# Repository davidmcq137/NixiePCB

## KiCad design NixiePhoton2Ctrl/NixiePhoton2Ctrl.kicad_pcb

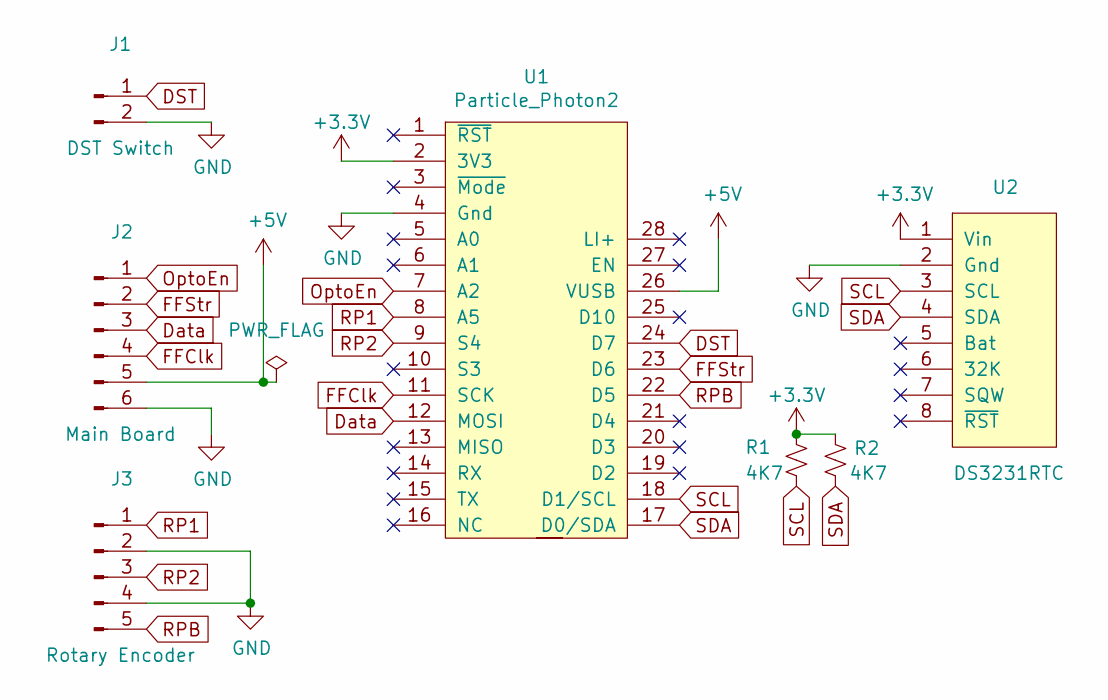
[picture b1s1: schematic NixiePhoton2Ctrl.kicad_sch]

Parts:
J1: DST Switch; PinHeader_1x02_P2.54mm_Vertical
J2: Main Board; PinHeader_1x06_P2.54mm_Vertical
J3: Rotary Encoder; PinHeader_1x05_P2.54mm_Vertical
R1, R2: 4K7; R_Axial_DIN0207_L6.3mm_D2.5mm_P7.62mm_Horizontal
U1: Particle_Photon2
U2: DS3231RTC

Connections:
+3V3: R1.1, R2.1, U1.2 (3V3), U2.1 (Vin)
+5V: J2.5, U1.26 (VUSB)
DST: J1.1, U1.24 (D7)
Data: J2.3, U1.12 (MOSI)
FFClk: J2.4, U1.11 (SCK)
FFStr: J2.2, U1.23 (D6)
GND: J1.2, J2.6, J3.2, J3.4, U1.4 (Gnd), U2.2 (Gnd)
OptoEn: J2.1, U1.7 (A2)
RP1: J3.1, U1.8 (A5)
RP2: J3.3, U1.9 (S4)
RPB: J3.5, U1.22 (D5)
SCL: R1.2, U1.18 (D1/SCL), U2.3 (SCL)
SDA: R2.2, U1.17 (D0/SDA), U2.4 (SDA)

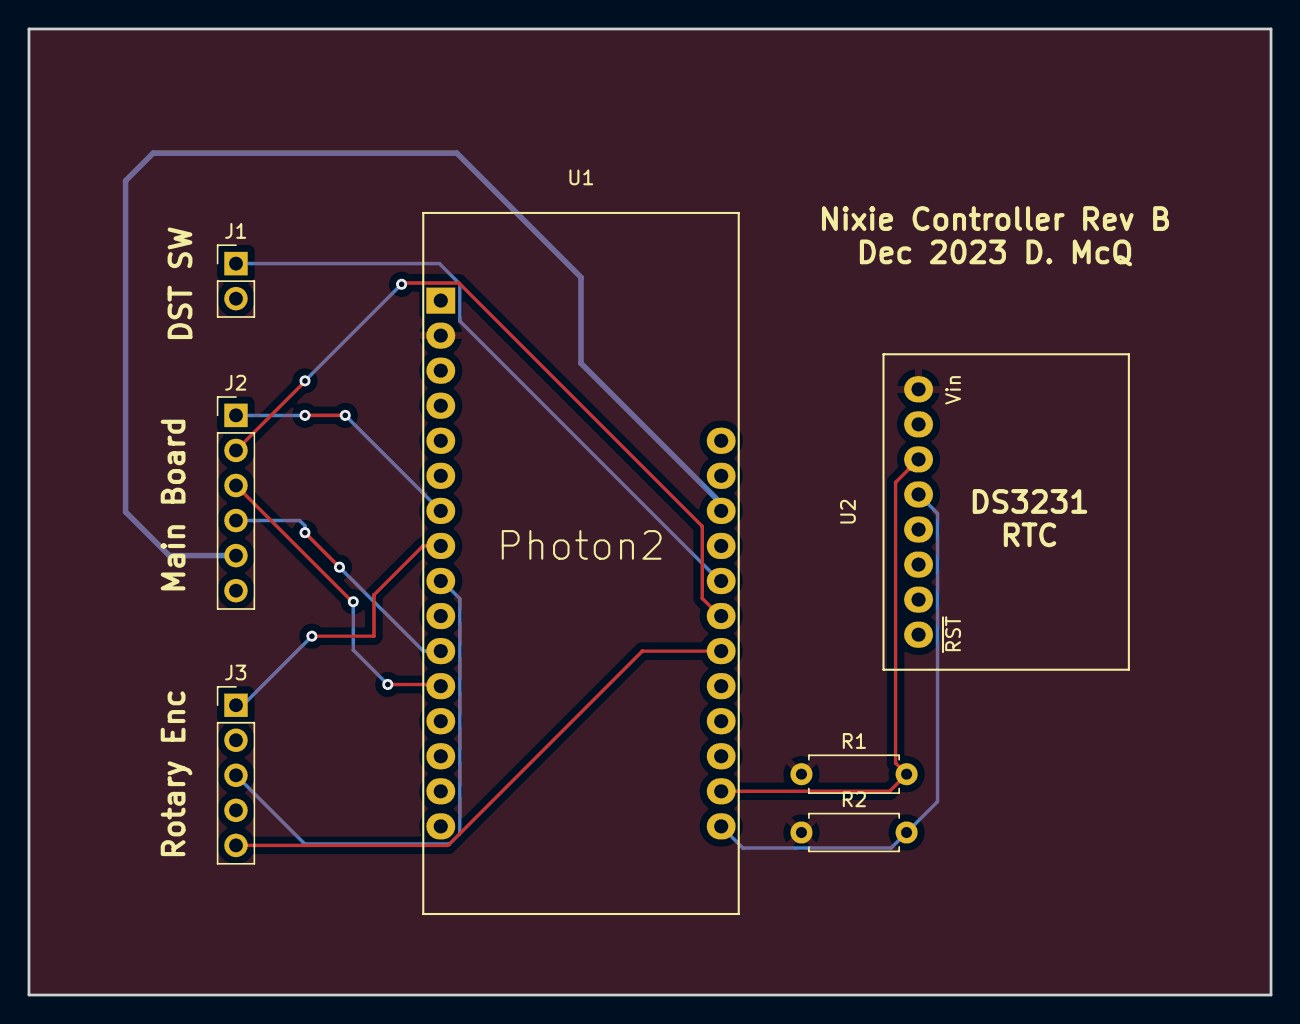
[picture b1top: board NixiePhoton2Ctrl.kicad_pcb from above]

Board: 2 copper layers, 90.0 x 70.0 mm, 7 parts (0 on the bottom side), 13 nets.

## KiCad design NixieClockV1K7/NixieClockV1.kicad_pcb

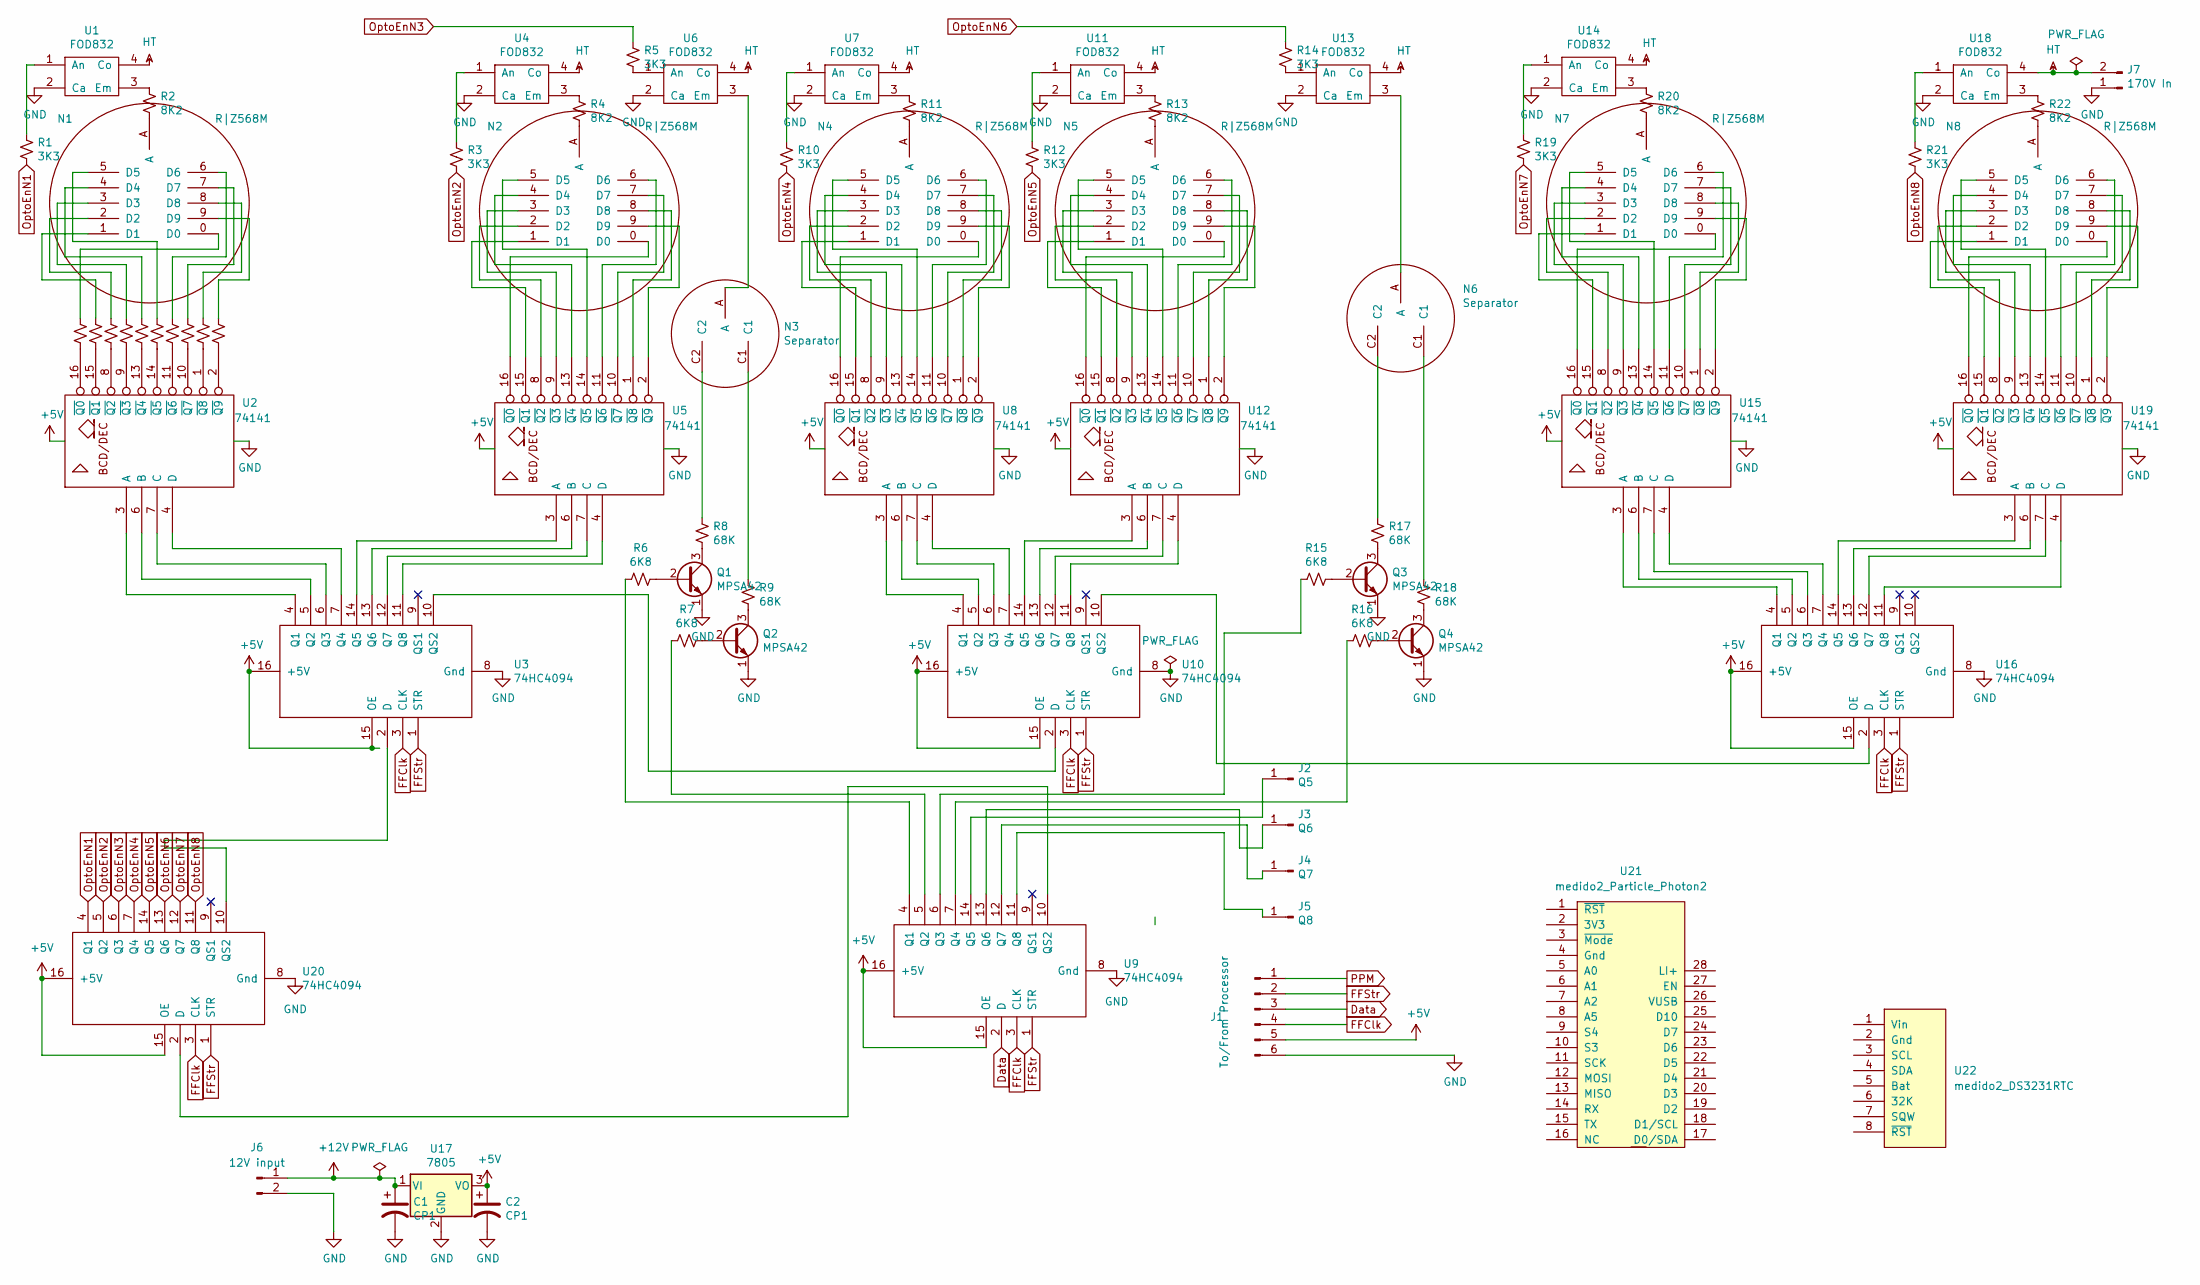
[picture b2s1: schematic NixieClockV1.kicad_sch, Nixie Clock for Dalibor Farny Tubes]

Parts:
C1, C2: CP1; CP_Radial_D7.5mm_P2.50mm
J1: To/From Processor; PinHeader_1x06_P2.54mm_Vertical
J2: Q5; PinHeader_1x01_P2.54mm_Vertical
J3: Q6; PinHeader_1x01_P2.54mm_Vertical
J4: Q7; PinHeader_1x01_P2.54mm_Vertical
J5: Q8; PinHeader_1x01_P2.54mm_Vertical
J6: 12V input; PinHeader_1x02_P2.54mm_Vertical
J7: 170V In; PinHeader_1x02_P2.54mm_Vertical
N1, N2, N4, N5, N7, N8: R|Z568M; RZ568M
N3, N6: Separator
Q1, Q2, Q3, Q4: MPSA42; TO-92L_Inline_Wide
R1, R3, R5, R10, R12, R14, R19, R21: 3K3; R_Axial_DIN0207_L6.3mm_D2.5mm_P10.16mm_Horizontal
R2, R4, R11, R13, R20, R22: 8K2; R_Axial_DIN0207_L6.3mm_D2.5mm_P10.16mm_Horizontal
R6, R7, R15, R16: 6K8; R_Axial_DIN0207_L6.3mm_D2.5mm_P10.16mm_Horizontal
R8, R9, R17, R18: 68K; R_Axial_DIN0207_L6.3mm_D2.5mm_P10.16mm_Horizontal
R23: 1; R_1210_3225Metric_Pad1.30x2.65mm_HandSolder
R24, R25, R26, R27, R28, R29, R30, R31, R32: R_Small_US; R_1210_3225Metric_Pad1.30x2.65mm_HandSolder
U1, U4, U6, U7, U11, U13, U14, U18: FOD832; DIP-4_W7.62mm
U2, U5, U8, U12, U15, U19: 74141; DIP-16_W7.62mm_Socket
U3, U9, U10, U20: 74HC4094; DIP-16_W7.62mm
U16: 74HC4094; DIP-16_W7.62mm_Socket
U17: 7805; TO-220-3_Vertical
U21: medido2_Particle_Photon2
U22: medido2_DS3231RTC

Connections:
+12V: C1.1, J6.1, U17.1 (VI)
Data: J1.3, U9.2 (D)
FFClk: J1.4, U3.3 (CLK), U9.3 (CLK), U10.3 (CLK), U16.3 (CLK), U20.3 (CLK)
FFStr: J1.2, U3.1 (STR), U9.1 (STR), U10.1 (STR), U16.1 (STR), U20.1 (STR)
GND: C1.2, C2.2, J1.6, J6.2, J7.1, Q1.1 (E), Q2.1 (E), Q3.1 (E), Q4.1 (E), U1.2 (Ca), U2.12 (GND), U3.8 (Gnd), U4.2 (Ca), U5.12 (GND), U6.2 (Ca), U7.2 (Ca), U8.12 (GND), U9.8 (Gnd), U10.8 (Gnd), U11.2 (Ca), U12.12 (GND), U13.2 (Ca), U14.2 (Ca), U15.12 (GND), U16.8 (Gnd), U17.2 (GND), U18.2 (Ca), U19.12 (GND), U20.8 (Gnd)
HT: J7.2, U1.4 (Co), U4.4 (Co), U6.4 (Co), U7.4 (Co), U11.4 (Co), U13.4 (Co), U14.4 (Co), U18.4 (Co)
unnamed: J2.1, U9.14 (Q5)
unnamed: J3.1, U9.13 (Q6)
unnamed: J4.1, U9.12 (Q7)
unnamed: J5.1, U9.11 (Q8)
unnamed: N1.0 (D0), R23.1
unnamed: N1.1 (D1), R24.2
unnamed: N1.2 (D2), R25.1
unnamed: N1.3 (D3), R26.1
unnamed: N1.4 (D4), R27.1
unnamed: N1.5 (D5), R28.1
unnamed: N1.6 (D6), R29.1
unnamed: N1.7 (D7), R30.1
unnamed: N1.8 (D8), R31.1
unnamed: N1.9 (D9), R32.1
unnamed: N1.A, R2.2
unnamed: N2.0 (D0), U5.16 (~Q0)
unnamed: N2.1 (D1), U5.15 (~Q1)
unnamed: N2.2 (D2), U5.8 (~Q2)
unnamed: N2.3 (D3), U5.9 (~Q3)
unnamed: N2.4 (D4), U5.13 (~Q4)
unnamed: N2.5 (D5), U5.14 (~Q5)
unnamed: N2.6 (D6), U5.11 (~Q6)
unnamed: N2.7 (D7), U5.10 (~Q7)
unnamed: N2.8 (D8), U5.1 (~Q8)
unnamed: N2.9 (D9), U5.2 (~Q9)
unnamed: N2.A, R4.2
unnamed: N3.C1, R9.1
unnamed: N3.C2, R8.1
unnamed: N4.0 (D0), U8.16 (~Q0)
unnamed: N4.1 (D1), U8.15 (~Q1)
unnamed: N4.2 (D2), U8.8 (~Q2)
unnamed: N4.3 (D3), U8.9 (~Q3)
unnamed: N4.4 (D4), U8.13 (~Q4)
unnamed: N4.5 (D5), U8.14 (~Q5)
unnamed: N4.6 (D6), U8.11 (~Q6)
unnamed: N4.7 (D7), U8.10 (~Q7)
unnamed: N4.8 (D8), U8.1 (~Q8)
unnamed: N4.9 (D9), U8.2 (~Q9)
unnamed: N4.A, R11.2
unnamed: N5.0 (D0), U12.16 (~Q0)
unnamed: N5.1 (D1), U12.15 (~Q1)
unnamed: N5.2 (D2), U12.8 (~Q2)
unnamed: N5.3 (D3), U12.9 (~Q3)
unnamed: N5.4 (D4), U12.13 (~Q4)
unnamed: N5.5 (D5), U12.14 (~Q5)
unnamed: N5.6 (D6), U12.11 (~Q6)
unnamed: N5.7 (D7), U12.10 (~Q7)
unnamed: N5.8 (D8), U12.1 (~Q8)
unnamed: N5.9 (D9), U12.2 (~Q9)
unnamed: N5.A, R13.2
unnamed: N6.C1, R18.1
unnamed: N6.C2, R17.1
unnamed: N7.0 (D0), U15.16 (~Q0)
unnamed: N7.1 (D1), U15.15 (~Q1)
unnamed: N7.2 (D2), U15.8 (~Q2)
unnamed: N7.3 (D3), U15.9 (~Q3)
unnamed: N7.4 (D4), U15.13 (~Q4)
unnamed: N7.5 (D5), U15.14 (~Q5)
unnamed: N7.6 (D6), U15.11 (~Q6)
unnamed: N7.7 (D7), U15.10 (~Q7)
unnamed: N7.8 (D8), U15.1 (~Q8)
unnamed: N7.9 (D9), U15.2 (~Q9)
unnamed: N7.A, R20.2
unnamed: N8.0 (D0), U19.16 (~Q0)
unnamed: N8.1 (D1), U19.15 (~Q1)
unnamed: N8.2 (D2), U19.8 (~Q2)
unnamed: N8.3 (D3), U19.9 (~Q3)
unnamed: N8.4 (D4), U19.13 (~Q4)
unnamed: N8.5 (D5), U19.14 (~Q5)
unnamed: N8.6 (D6), U19.11 (~Q6)
unnamed: N8.7 (D7), U19.10 (~Q7)
unnamed: N8.8 (D8), U19.1 (~Q8)
unnamed: N8.9 (D9), U19.2 (~Q9)
unnamed: N8.A, R22.2
unnamed: Q1.2 (B), R6.1
unnamed: Q1.3 (C), R8.2
unnamed: Q2.2 (B), R7.1
unnamed: Q2.3 (C), R9.2
unnamed: Q3.2 (B), R15.1
unnamed: Q3.3 (C), R17.2
unnamed: Q4.2 (B), R16.1
unnamed: Q4.3 (C), R18.2
unnamed: R1.1, U1.1 (An)
unnamed: R2.1, U1.3 (Em)
unnamed: U2.3 (A), U3.4 (Q1)
unnamed: U2.6 (B), U3.5 (Q2)
unnamed: U2.7 (C), U3.6 (Q3)
unnamed: U2.4 (D), U3.7 (Q4)
unnamed: R23.2, U2.16 (~Q0)
unnamed: R24.1, U2.15 (~Q1)
unnamed: R25.2, U2.8 (~Q2)
unnamed: R26.2, U2.9 (~Q3)
unnamed: R27.2, U2.13 (~Q4)
unnamed: R28.2, U2.14 (~Q5)
unnamed: R29.2, U2.11 (~Q6)
unnamed: R30.2, U2.10 (~Q7)
unnamed: R31.2, U2.1 (~Q8)
unnamed: R32.2, U2.2 (~Q9)
unnamed: U3.14 (Q5), U5.3 (A)
unnamed: U3.13 (Q6), U5.6 (B)
unnamed: U3.12 (Q7), U5.7 (C)
unnamed: U3.11 (Q8), U5.4 (D)
unnamed: R3.1, U4.1 (An)
unnamed: R4.1, U4.3 (Em)
unnamed: R5.2, U6.1 (An)
unnamed: N3.A, U6.3 (Em)
unnamed: R10.1, U7.1 (An)
unnamed: R11.1, U7.3 (Em)
unnamed: R6.2, U9.4 (Q1)
unnamed: R7.2, U9.5 (Q2)
unnamed: R15.2, U9.6 (Q3)
unnamed: R16.2, U9.7 (Q4)
unnamed: U3.10 (QS2), U10.2 (D)
unnamed: U8.3 (A), U10.4 (Q1)
unnamed: U8.6 (B), U10.5 (Q2)
unnamed: U8.7 (C), U10.6 (Q3)
unnamed: U8.4 (D), U10.7 (Q4)
unnamed: U10.14 (Q5), U12.3 (A)
unnamed: U10.13 (Q6), U12.6 (B)
unnamed: U10.12 (Q7), U12.7 (C)
unnamed: U10.11 (Q8), U12.4 (D)
unnamed: U10.10 (QS2), U16.2 (D)
unnamed: R12.1, U11.1 (An)
unnamed: R13.1, U11.3 (Em)
unnamed: R14.2, U13.1 (An)
unnamed: N6.A, U13.3 (Em)
unnamed: R19.1, U14.1 (An)
unnamed: R20.1, U14.3 (Em)
unnamed: U15.3 (A), U16.4 (Q1)
unnamed: U15.6 (B), U16.5 (Q2)
unnamed: U15.7 (C), U16.6 (Q3)
unnamed: U15.4 (D), U16.7 (Q4)
unnamed: U16.14 (Q5), U19.3 (A)
unnamed: U16.13 (Q6), U19.6 (B)
unnamed: U16.12 (Q7), U19.7 (C)
unnamed: U16.11 (Q8), U19.4 (D)
unnamed: R21.1, U18.1 (An)
unnamed: R22.1, U18.3 (Em)
unnamed: U9.10 (QS2), U20.2 (D)
unnamed: U3.2 (D), U20.10 (QS2)
OptoEnN1: R1.2, U20.4 (Q1)
OptoEnN2: R3.2, U20.5 (Q2)
OptoEnN3: R5.1, U20.6 (Q3)
OptoEnN4: R10.2, U20.7 (Q4)
OptoEnN5: R12.2, U20.14 (Q5)
OptoEnN6: R14.1, U20.13 (Q6)
OptoEnN7: R19.2, U20.12 (Q7)
OptoEnN8: R21.2, U20.11 (Q8)
PPM: J1.1

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
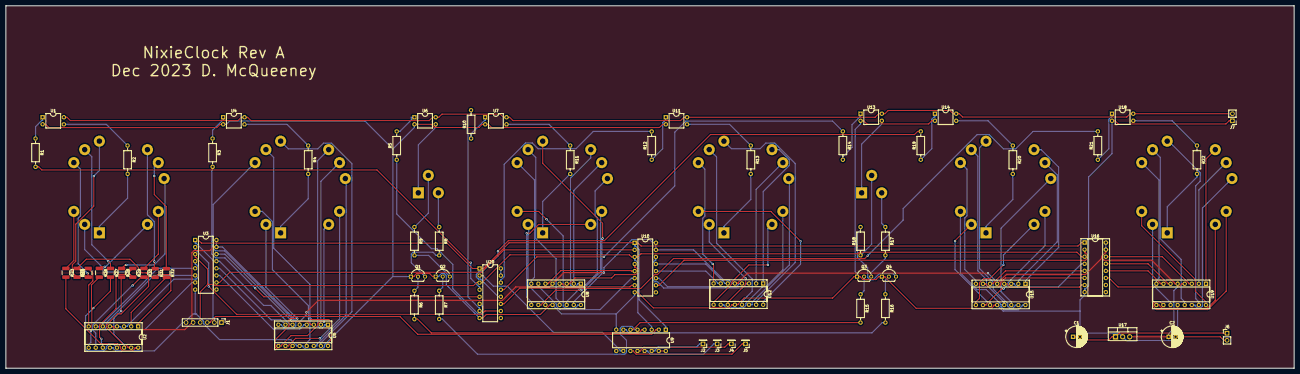
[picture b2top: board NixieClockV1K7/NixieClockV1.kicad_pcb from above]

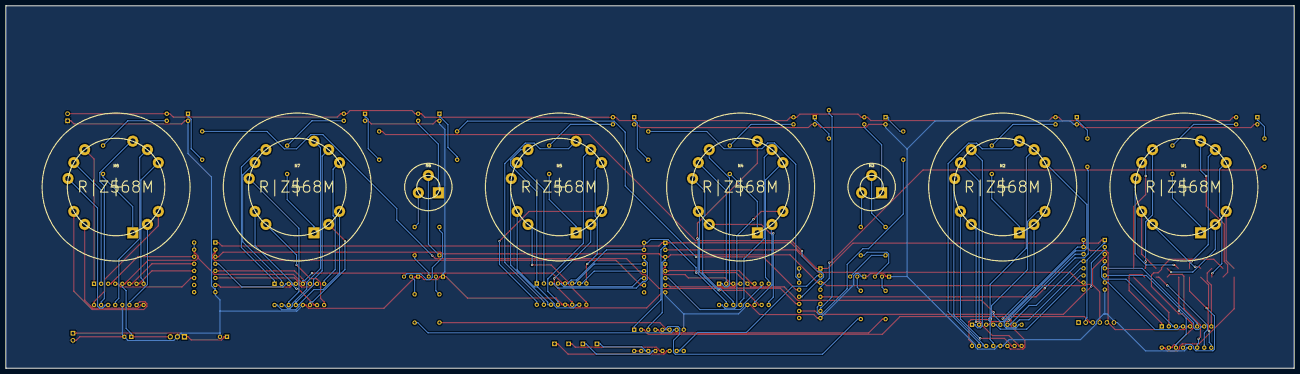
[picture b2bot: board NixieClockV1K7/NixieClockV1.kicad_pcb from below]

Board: 2 copper layers, 462.1 x 130.0 mm, 73 parts (8 on the bottom side), 157 nets.

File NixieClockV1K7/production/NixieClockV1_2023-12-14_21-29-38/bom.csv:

Designator,Footprint,Quantity,Value,LCSC Part #
"C1, C2",CP_Radial_D7.5mm_P2.50mm,2,CP1,
J1,PinHeader_1x06_P2.54mm_Vertical,1,To/From Processor,
J2,PinHeader_1x01_P2.54mm_Vertical,1,Q5,
J3,PinHeader_1x01_P2.54mm_Vertical,1,Q6,
J4,PinHeader_1x01_P2.54mm_Vertical,1,Q7,
J5,PinHeader_1x01_P2.54mm_Vertical,1,Q8,
J6,PinHeader_1x02_P2.54mm_Vertical,1,12V input,
J7,PinHeader_1x02_P2.54mm_Vertical,1,170V In,
"N1, N2, N4, N5, N7, N8",RZ568M,6,R|Z568M,
"N3, N6",Separator,2,Separator,
"Q1, Q2, Q3, Q4",TO-92L_Inline_Wide,4,MPSA42,
"R1, R10, R12, R14, R19, R21, R3, R5",R_Axial_DIN0207_L6.3mm_D2.5mm_P10.16mm_Horizontal,8,3K3,
"R11, R13, R2, R20, R22, R4",R_Axial_DIN0207_L6.3mm_D2.5mm_P10.16mm_Horizontal,6,8K2,
"R15, R16, R6, R7",R_Axial_DIN0207_L6.3mm_D2.5mm_P10.16mm_Horizontal,4,6K8,
"R17, R18, R8, R9",R_Axial_DIN0207_L6.3mm_D2.5mm_P10.16mm_Horizontal,4,68K,
R23,1210,1,1,
"R24, R25, R26, R27, R28, R29, R30, R31, R32",1210,9,R_Small_US,
"U1, U11, U13, U14, U18, U4, U6, U7",DIP-4_W7.62mm,8,FOD832,
"U10, U20, U3, U9",DIP-16_W7.62mm,4,74HC4094,
"U12, U15, U19, U2, U5, U8",DIP-16_W7.62mm_Socket,6,74141,
U16,DIP-16_W7.62mm_Socket,1,74HC4094,
U17,TO-220-3_Vertical,1,7805,

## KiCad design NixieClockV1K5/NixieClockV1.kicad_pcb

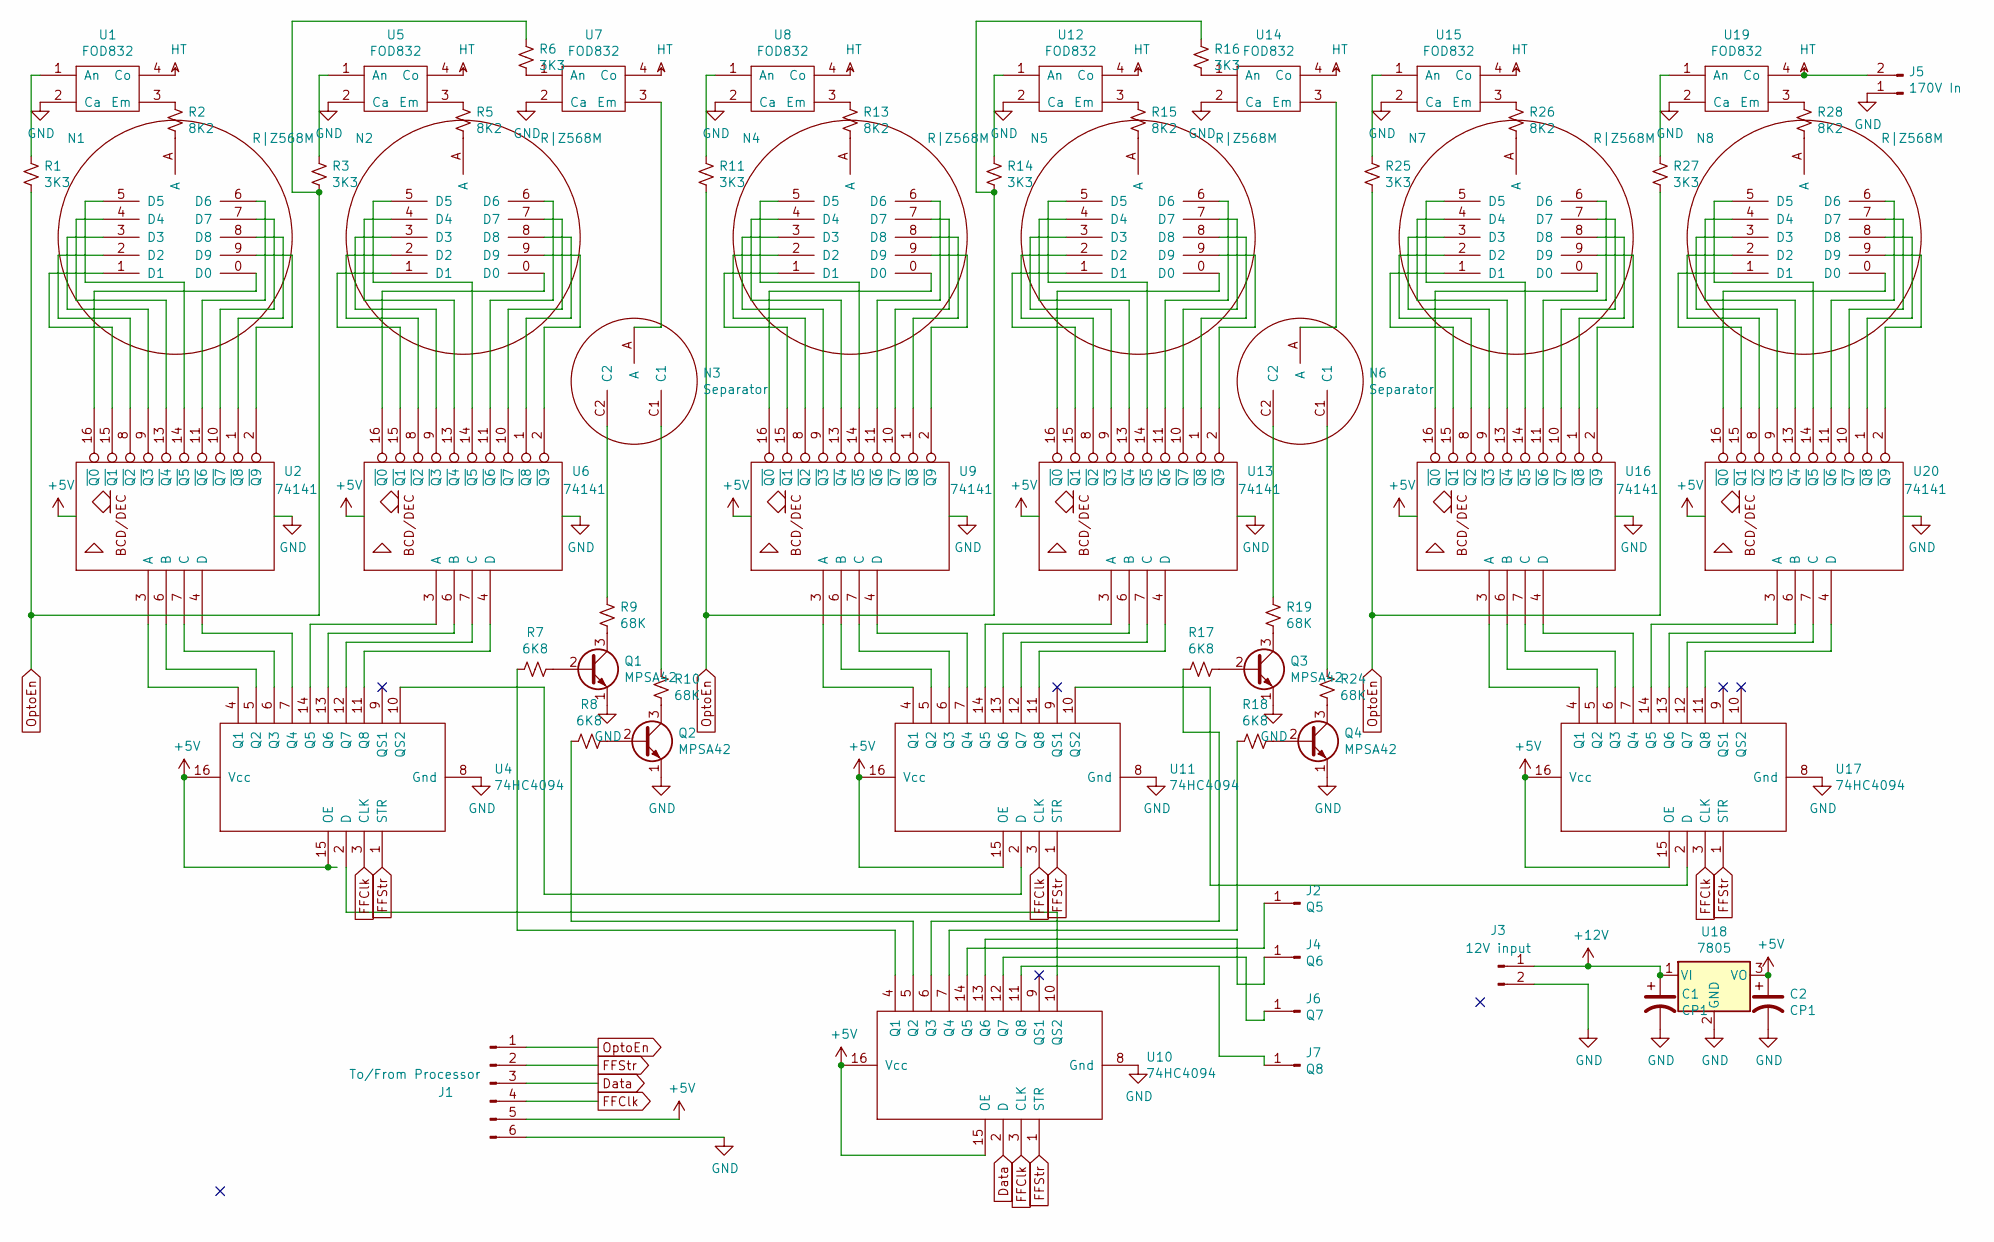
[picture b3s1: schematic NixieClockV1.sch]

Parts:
C1, C2: CP1; CP_Radial_D7.5mm_P2.50mm
J1: To/From Processor; PinHeader_1x06_P2.54mm_Vertical
J2: Q5; PinHeader_1x01_P2.54mm_Vertical
J3: 12V input; PinHeader_1x02_P2.54mm_Vertical
J4: Q6; PinHeader_1x01_P2.54mm_Vertical
J5: 170V In; PinHeader_1x02_P2.54mm_Vertical
J6: Q7; PinHeader_1x01_P2.54mm_Vertical
J7: Q8; PinHeader_1x01_P2.54mm_Vertical
N1, N2, N4, N5, N7, N8: R|Z568M; RZ568M
N3, N6: Separator
Q1, Q2, Q3, Q4: MPSA42; TO-92_Inline
R1, R3, R6, R11, R14, R16, R25, R27: 3K3; R_Axial_DIN0207_L6.3mm_D2.5mm_P10.16mm_Horizontal
R2, R5, R13, R15, R26, R28: 8K2; R_Axial_DIN0207_L6.3mm_D2.5mm_P10.16mm_Horizontal
R7, R8, R17, R18: 6K8; R_Axial_DIN0207_L6.3mm_D2.5mm_P10.16mm_Horizontal
R9, R10, R19, R24: 68K; R_Axial_DIN0207_L6.3mm_D2.5mm_P10.16mm_Horizontal
U1, U5, U7, U8, U12, U14, U15, U19: FOD832; DIP-4_W7.62mm
U2, U6, U9, U13, U16, U20: 74141; DIP-16_W7.62mm_Socket
U4, U10, U11: 74HC4094; DIP-16_W7.62mm
U17: 74HC4094; DIP-16_W7.62mm_Socket
U18: 7805; TO-220-3_Vertical

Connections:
+5V: C2.1, J1.5, U2.5 (VCC), U4.15 (OE), U4.16 (Vcc), U6.5 (VCC), U9.5 (VCC), U10.15 (OE), U10.16 (Vcc), U11.15 (OE), U11.16 (Vcc), U13.5 (VCC), U16.5 (VCC), U17.15 (OE), U17.16 (Vcc), U18.3 (VO), U20.5 (VCC)
+12V: C1.1, J3.1, U18.1 (VI)
Data: J1.3, U10.2 (D)
FFClk: J1.4, U4.3 (CLK), U10.3 (CLK), U11.3 (CLK), U17.3 (CLK)
FFStr: J1.2, U4.1 (STR), U10.1 (STR), U11.1 (STR), U17.1 (STR)
GND: C1.2, C2.2, J1.6, J3.2, J5.1, Q1.1 (E), Q2.1 (E), Q3.1 (E), Q4.1 (E), U1.2 (Ca), U2.12 (GND), U4.8 (Gnd), U5.2 (Ca), U6.12 (GND), U7.2 (Ca), U8.2 (Ca), U9.12 (GND), U10.8 (Gnd), U11.8 (Gnd), U12.2 (Ca), U13.12 (GND), U14.2 (Ca), U15.2 (Ca), U16.12 (GND), U17.8 (Gnd), U18.2 (GND), U19.2 (Ca), U20.12 (GND)
HT: J5.2, U1.4 (Co), U5.4 (Co), U7.4 (Co), U8.4 (Co), U12.4 (Co), U14.4 (Co), U15.4 (Co), U19.4 (Co)
unnamed: J2.1, U10.14 (Q5)
unnamed: J4.1, U10.13 (Q6)
unnamed: J6.1, U10.12 (Q7)
unnamed: J7.1, U10.11 (Q8)
unnamed: N1.0 (D0), U2.16 (~Q0)
unnamed: N1.1 (D1), U2.15 (~Q1)
unnamed: N1.2 (D2), U2.8 (~Q2)
unnamed: N1.3 (D3), U2.9 (~Q3)
unnamed: N1.4 (D4), U2.13 (~Q4)
unnamed: N1.5 (D5), U2.14 (~Q5)
unnamed: N1.6 (D6), U2.11 (~Q6)
unnamed: N1.7 (D7), U2.10 (~Q7)
unnamed: N1.8 (D8), U2.1 (~Q8)
unnamed: N1.9 (D9), U2.2 (~Q9)
unnamed: N1.A, R2.2
unnamed: N2.0 (D0), U6.16 (~Q0)
unnamed: N2.1 (D1), U6.15 (~Q1)
unnamed: N2.2 (D2), U6.8 (~Q2)
unnamed: N2.3 (D3), U6.9 (~Q3)
unnamed: N2.4 (D4), U6.13 (~Q4)
unnamed: N2.5 (D5), U6.14 (~Q5)
unnamed: N2.6 (D6), U6.11 (~Q6)
unnamed: N2.7 (D7), U6.10 (~Q7)
unnamed: N2.8 (D8), U6.1 (~Q8)
unnamed: N2.9 (D9), U6.2 (~Q9)
unnamed: N2.A, R5.2
unnamed: N3.A, U7.3 (Em)
unnamed: N3.C1, R10.1
unnamed: N3.C2, R9.1
unnamed: N4.0 (D0), U9.16 (~Q0)
unnamed: N4.1 (D1), U9.15 (~Q1)
unnamed: N4.2 (D2), U9.8 (~Q2)
unnamed: N4.3 (D3), U9.9 (~Q3)
unnamed: N4.4 (D4), U9.13 (~Q4)
unnamed: N4.5 (D5), U9.14 (~Q5)
unnamed: N4.6 (D6), U9.11 (~Q6)
unnamed: N4.7 (D7), U9.10 (~Q7)
unnamed: N4.8 (D8), U9.1 (~Q8)
unnamed: N4.9 (D9), U9.2 (~Q9)
unnamed: N4.A, R13.2
unnamed: N5.0 (D0), U13.16 (~Q0)
unnamed: N5.1 (D1), U13.15 (~Q1)
unnamed: N5.2 (D2), U13.8 (~Q2)
unnamed: N5.3 (D3), U13.9 (~Q3)
unnamed: N5.4 (D4), U13.13 (~Q4)
unnamed: N5.5 (D5), U13.14 (~Q5)
unnamed: N5.6 (D6), U13.11 (~Q6)
unnamed: N5.7 (D7), U13.10 (~Q7)
unnamed: N5.8 (D8), U13.1 (~Q8)
unnamed: N5.9 (D9), U13.2 (~Q9)
unnamed: N5.A, R15.2
unnamed: N6.A, U14.3 (Em)
unnamed: N6.C1, R24.1
unnamed: N6.C2, R19.1
unnamed: N7.0 (D0), U16.16 (~Q0)
unnamed: N7.1 (D1), U16.15 (~Q1)
unnamed: N7.2 (D2), U16.8 (~Q2)
unnamed: N7.3 (D3), U16.9 (~Q3)
unnamed: N7.4 (D4), U16.13 (~Q4)
unnamed: N7.5 (D5), U16.14 (~Q5)
unnamed: N7.6 (D6), U16.11 (~Q6)
unnamed: N7.7 (D7), U16.10 (~Q7)
unnamed: N7.8 (D8), U16.1 (~Q8)
unnamed: N7.9 (D9), U16.2 (~Q9)
unnamed: N7.A, R26.2
unnamed: N8.0 (D0), U20.16 (~Q0)
unnamed: N8.1 (D1), U20.15 (~Q1)
unnamed: N8.2 (D2), U20.8 (~Q2)
unnamed: N8.3 (D3), U20.9 (~Q3)
unnamed: N8.4 (D4), U20.13 (~Q4)
unnamed: N8.5 (D5), U20.14 (~Q5)
unnamed: N8.6 (D6), U20.11 (~Q6)
unnamed: N8.7 (D7), U20.10 (~Q7)
unnamed: N8.8 (D8), U20.1 (~Q8)
unnamed: N8.9 (D9), U20.2 (~Q9)
unnamed: N8.A, R28.2
unnamed: Q1.2 (B), R7.1
unnamed: Q1.3 (C), R9.2
unnamed: Q2.2 (B), R8.1
unnamed: Q2.3 (C), R10.2
unnamed: Q3.2 (B), R17.1
unnamed: Q3.3 (C), R19.2
unnamed: Q4.2 (B), R18.1
unnamed: Q4.3 (C), R24.2
unnamed: R1.1, U1.1 (An)
unnamed: R2.1, U1.3 (Em)
unnamed: R3.1, U5.1 (An)
unnamed: R5.1, U5.3 (Em)
unnamed: R6.2, U7.1 (An)
unnamed: R7.2, U10.4 (Q1)
unnamed: R8.2, U10.5 (Q2)
unnamed: R11.1, U8.1 (An)
unnamed: R13.1, U8.3 (Em)
unnamed: R14.1, U12.1 (An)
unnamed: R15.1, U12.3 (Em)
unnamed: R16.2, U14.1 (An)
unnamed: R17.2, U10.6 (Q3)
unnamed: R18.2, U10.7 (Q4)
unnamed: R25.1, U15.1 (An)
unnamed: R26.1, U15.3 (Em)
unnamed: R27.1, U19.1 (An)
unnamed: R28.1, U19.3 (Em)
unnamed: U2.3 (A), U4.4 (Q1)
unnamed: U2.4 (D), U4.7 (Q4)
unnamed: U2.6 (B), U4.5 (Q2)
unnamed: U2.7 (C), U4.6 (Q3)
unnamed: U4.11 (Q8), U6.4 (D)
unnamed: U4.12 (Q7), U6.7 (C)
unnamed: U4.13 (Q6), U6.6 (B)
unnamed: U4.14 (Q5), U6.3 (A)
unnamed: U4.2 (D), U10.10 (QS2)
unnamed: U4.10 (QS2), U11.2 (D)
unnamed: U9.3 (A), U11.4 (Q1)
unnamed: U9.6 (B), U11.5 (Q2)
unnamed: U9.7 (C), U11.6 (Q3)
unnamed: U9.4 (D), U11.7 (Q4)
unnamed: U11.10 (QS2), U17.2 (D)
unnamed: U11.11 (Q8), U13.4 (D)
unnamed: U11.12 (Q7), U13.7 (C)
unnamed: U11.13 (Q6), U13.6 (B)
unnamed: U11.14 (Q5), U13.3 (A)
unnamed: U16.3 (A), U17.4 (Q1)
unnamed: U16.4 (D), U17.7 (Q4)
unnamed: U16.6 (B), U17.5 (Q2)
unnamed: U16.7 (C), U17.6 (Q3)
unnamed: U17.11 (Q8), U20.4 (D)
unnamed: U17.12 (Q7), U20.7 (C)
unnamed: U17.13 (Q6), U20.6 (B)
unnamed: U17.14 (Q5), U20.3 (A)
OptoEn: J1.1, R1.2, R3.2, R6.1, R11.2, R14.2, R16.1, R25.2, R27.2

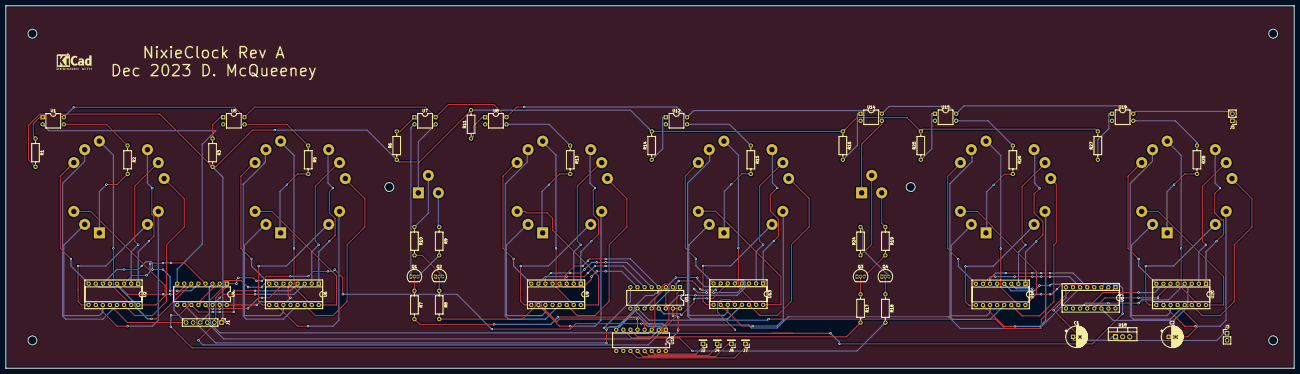
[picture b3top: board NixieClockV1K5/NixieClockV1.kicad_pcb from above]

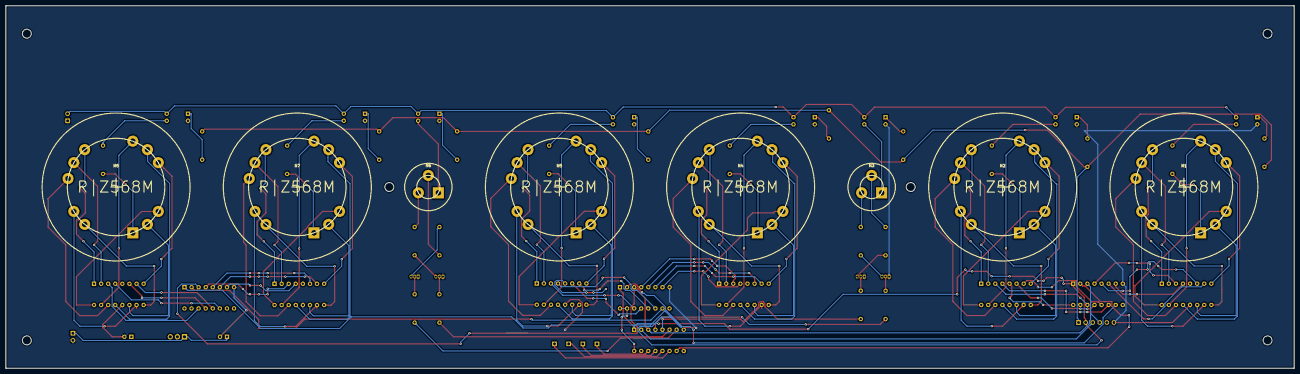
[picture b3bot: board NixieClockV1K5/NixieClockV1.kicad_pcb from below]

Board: 2 copper layers, 462.1 x 130.0 mm, 62 parts (8 on the bottom side), 137 nets.

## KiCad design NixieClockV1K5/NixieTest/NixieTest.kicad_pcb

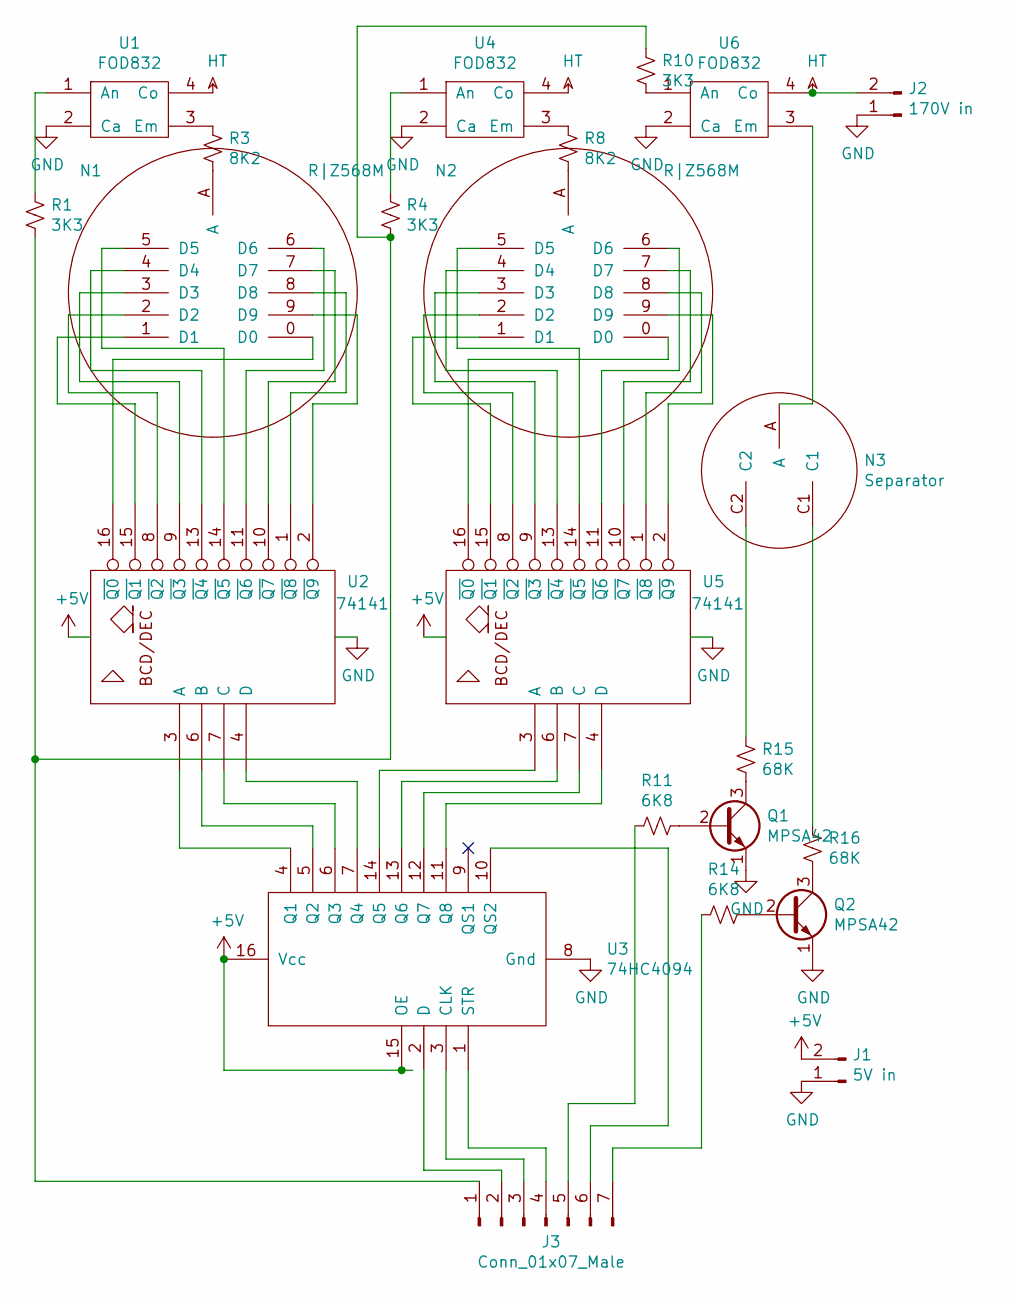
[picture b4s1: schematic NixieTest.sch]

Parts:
J1: 5V in; PinHeader_1x02_P2.54mm_Vertical
J2: 170V in; PinHeader_1x02_P2.54mm_Vertical
J3: Conn_01x07_Male; PinHeader_1x07_P2.54mm_Vertical
N1, N2: R|Z568M; RZ568M
N3: Separator
Q1, Q2: MPSA42; TO-92_Inline
R1, R4, R10: 3K3; R_Axial_DIN0207_L6.3mm_D2.5mm_P10.16mm_Horizontal
R3, R8: 8K2; R_Axial_DIN0207_L6.3mm_D2.5mm_P10.16mm_Horizontal
R11, R14: 6K8; R_Axial_DIN0207_L6.3mm_D2.5mm_P10.16mm_Horizontal
R15, R16: 68K; R_Axial_DIN0207_L6.3mm_D2.5mm_P10.16mm_Horizontal
U1, U4, U6: FOD832; DIP-4_W7.62mm
U2, U5: 74141; DIP-16_W7.62mm_Socket
U3: 74HC4094; DIP-16_W7.62mm

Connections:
+5V: J1.2, U2.5 (VCC), U3.15 (OE), U3.16 (Vcc), U5.5 (VCC)
GND: J1.1, J2.1, Q1.1 (E), Q2.1 (E), U1.2 (Ca), U2.12 (GND), U3.8 (Gnd), U4.2 (Ca), U5.12 (GND), U6.2 (Ca)
HT: J2.2, U1.4 (Co), U4.4 (Co), U6.4 (Co)
unnamed: J3.1, R1.2, R4.2, R10.1
unnamed: J3.2, U3.2 (D)
unnamed: J3.3, U3.3 (CLK)
unnamed: J3.4, U3.1 (STR)
unnamed: J3.5, R11.2
unnamed: J3.6, U3.10 (QS2)
unnamed: J3.7, R14.2
unnamed: N1.0 (D0), U2.16 (~Q0)
unnamed: N1.1 (D1), U2.15 (~Q1)
unnamed: N1.2 (D2), U2.8 (~Q2)
unnamed: N1.3 (D3), U2.9 (~Q3)
unnamed: N1.4 (D4), U2.13 (~Q4)
unnamed: N1.5 (D5), U2.14 (~Q5)
unnamed: N1.6 (D6), U2.11 (~Q6)
unnamed: N1.7 (D7), U2.10 (~Q7)
unnamed: N1.8 (D8), U2.1 (~Q8)
unnamed: N1.9 (D9), U2.2 (~Q9)
unnamed: N1.A, R3.2
unnamed: N2.0 (D0), U5.16 (~Q0)
unnamed: N2.1 (D1), U5.15 (~Q1)
unnamed: N2.2 (D2), U5.8 (~Q2)
unnamed: N2.3 (D3), U5.9 (~Q3)
unnamed: N2.4 (D4), U5.13 (~Q4)
unnamed: N2.5 (D5), U5.14 (~Q5)
unnamed: N2.6 (D6), U5.11 (~Q6)
unnamed: N2.7 (D7), U5.10 (~Q7)
unnamed: N2.8 (D8), U5.1 (~Q8)
unnamed: N2.9 (D9), U5.2 (~Q9)
unnamed: N2.A, R8.2
unnamed: N3.A, U6.3 (Em)
unnamed: N3.C1, R16.1
unnamed: N3.C2, R15.1
unnamed: Q1.2 (B), R11.1
unnamed: Q1.3 (C), R15.2
unnamed: Q2.2 (B), R14.1
unnamed: Q2.3 (C), R16.2
unnamed: R1.1, U1.1 (An)
unnamed: R3.1, U1.3 (Em)
unnamed: R4.1, U4.1 (An)
unnamed: R8.1, U4.3 (Em)
unnamed: R10.2, U6.1 (An)
unnamed: U2.3 (A), U3.4 (Q1)
unnamed: U2.4 (D), U3.7 (Q4)
unnamed: U2.6 (B), U3.5 (Q2)
unnamed: U2.7 (C), U3.6 (Q3)
unnamed: U3.11 (Q8), U5.4 (D)
unnamed: U3.12 (Q7), U5.7 (C)
unnamed: U3.13 (Q6), U5.6 (B)
unnamed: U3.14 (Q5), U5.3 (A)

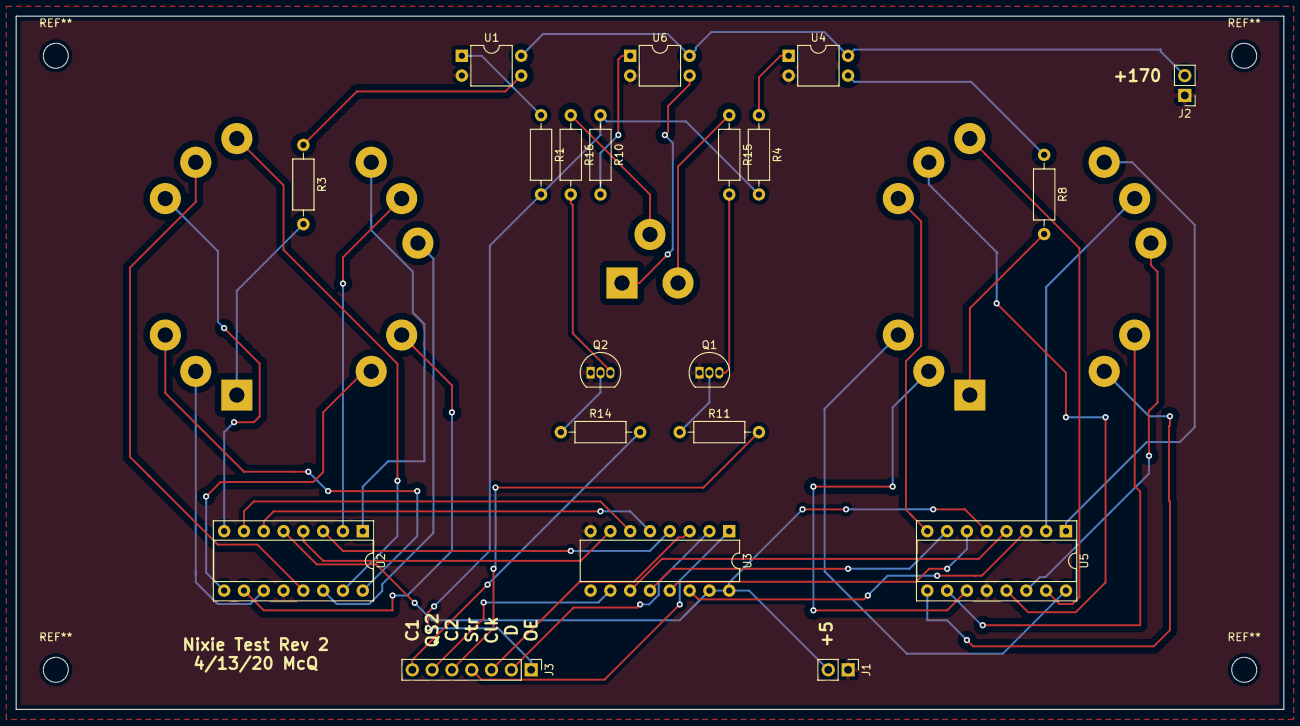
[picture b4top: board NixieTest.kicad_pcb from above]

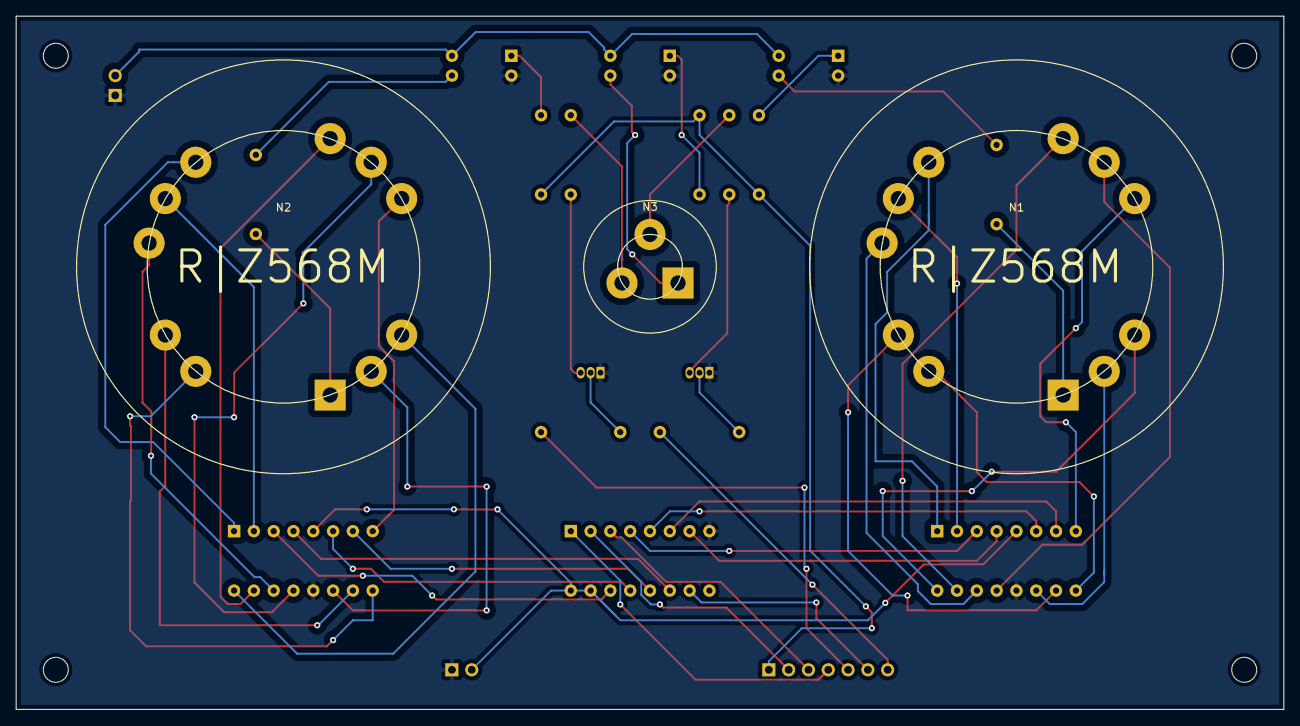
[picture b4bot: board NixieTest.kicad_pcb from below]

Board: 2 copper layers, 162.6 x 88.9 mm, 23 parts (3 on the bottom side), 52 nets.

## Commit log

2023-12-10 first push NixieClockV1
2023-12-10 first push NixiePhoton2Ctrl
2023-12-15 misc
